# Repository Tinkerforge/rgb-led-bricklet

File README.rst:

RGB LED Bricklet
================

This repository contains the firmware source code and the hardware design
files. The documentation generator configs can be found at
https://github.com/Tinkerforge/generators

Repository Content
------------------

software/:
 * examples/: Examples for all supported languages
 * build/: Compiled files
 * src/: Source code of firmware
 * Makefile: Makefile to build project

hardware/:
 * Contains KiCad project files and additionally schematics as PDF

datasheets/:
 * Contains datasheets for sensors and complex ICs that are used

Hardware
--------

The hardware is designed with the open source EDA Suite KiCad
(http://www.kicad.org). Before you are able to open the files,
you have to install the Tinkerforge kicad-libraries
(https://github.com/Tinkerforge/kicad-libraries). You can either clone
them directly in hardware/ or clone them in a separate folder and
symlink them into hardware/
(ln -s kicad_path/kicad-libraries project_path/hardware). After that you
can open the .pro file in hardware/ with KiCad and from there view and
modify the schematics and the PCB layout.

Software
--------

If you want to do your own Brick/Bricklet firmware development we highly
recommend that you use our build environment setup script and read the
tutorial (https://www.tinkerforge.com/en/doc/Tutorials/Tutorial_Build_Environment/Tutorial.html).

To compile the C code we recommend you to install the newest GNU Arm Embedded
Toolchain (https://launchpad.net/gcc-arm-embedded/+download).
You also need to install bricklib (https://github.com/Tinkerforge/bricklib)
and brickletlib (https://github.com/Tinkerforge/brickletlib).

You can either clone it directly in software/src/ or clone it in a
separate folder and symlink it into software/src/
(ln -s bricklib_path/bricklib project_path/software/src/ and
ln -s brickletlib_path/brickletlib project_path/software/src/).
Finally make sure to have CMake installed
(http://www.cmake.org/cmake/resources/software.html).

After that you can build the firmware by invoking make in software/.
The firmware (.bin) can then be found in software/build/ and uploaded
with brickv (click button "Flashing" on start screen).

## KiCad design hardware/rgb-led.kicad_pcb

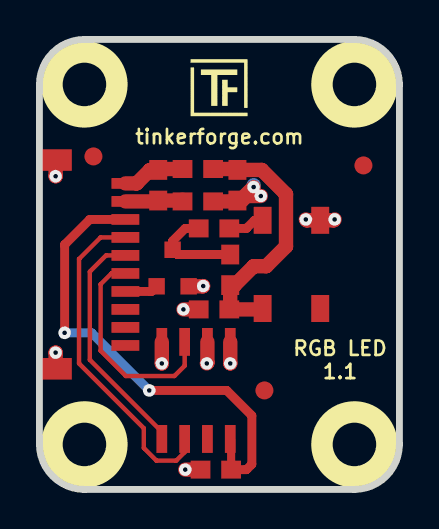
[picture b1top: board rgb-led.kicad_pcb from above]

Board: 2 copper layers, 20.0 x 25.0 mm, 20 parts (0 on the bottom side), 11 nets.

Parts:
C1, C2, C3, C4: 100nF; C0603E
FB1: FILTER; C0603E
Fiducial_Mark: VAL**; Fiducial_Mark
Fiducial_Mark#2, Fiducial_Mark#3: VAL**; Fiducial_Mark
LED1: WS2812B_LED
P1: CON-SENSOR
Q1: 2N7002P; SOT23GDS
R1: 1k; R0603E
R2: 0; R0603E
R3: 330; R0603E
U1: M24C64; SOIC8
U2, U3, U4, U5: DRILL; DRILL_NP
VAL: CE_5mm

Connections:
3V3: C4.1, P1.3, U1.8
GND: C2.1, C3.2, C4.2, LED1.3, P1.EP, Q1.S, R2.1, U1.1, U1.2, U1.4
unnamed: C1.1, P1.2, R2.2
unnamed: C1.2, FB1.1, P1.1
unnamed: LED1.4, R3.1
unnamed: P1.6, U1.3
unnamed: P1.7, Q1.G
unnamed: Q1.D, R1.1, R3.2
SCL: P1.4, U1.6
SDA: P1.5, U1.5
VCC: C2.2, C3.1, FB1.2, LED1.1, R1.2

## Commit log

2015-11-18 initial checkin of readme and license file
2015-11-18 prototype of rgb pixel bricklet
2015-11-23 fully routed, drc check
2016-02-09 Add WIP marker
2016-03-31 add fiducials
2016-06-10 Add RGB LED Bricklet plugin source
2016-06-10 Fix device identifier
2016-06-10 Add .gitignore
2016-06-17 add schematic
2016-06-27 Add examples
2016-07-01 Make the change UID comment more explicit
2016-07-13 Add changelog date and commit after the fact
2016-07-13 Add rainbow example
2016-07-13 Add WAS2812B datasheet
2016-07-14 Remove WIP marker
2016-08-04 fix rgb led bricklets dimensions
2016-08-04 increase version number to 1.1
2016-08-04 update schematic
2016-09-06 Fix green flash after reset
    MOSFET inverts logic, initial pin state needs to be high to ensure low
    output until first frame.
2016-09-06 Add changelog commit after the fact
2017-06-02 octave: Use javaObject instead of deprecated java_new
2017-08-01 Fix smybol
2017-08-01 Add 3d information (final)
2017-08-01 Add 3d model (*.step & *.FCStd)
2017-12-07 mathematica: Also generate .nb files
2018-02-19 javascript: Close div tag correctly
2018-02-20 Cleanup KiCad libraries config
    Ensure LibDir=kicad-libraries and LibName1=tinkerforge.
    Remove special library.
2018-05-24 perl: Use strict in examples
2018-07-11 Add Makefile with docker support
2018-07-11 Update directory structure and build instructions
2018-07-11 Remove obsolete generate_makefile scripts
2018-11-06 Add rust examples
2018-11-07 rust: Accept host names for ip connection, fix naming inconsistencies
2018-12-14 Add go examples.
2018-12-18 go: Change import path.
2018-12-18 go: Change import path again.
2018-12-20 rust: Reformat examples.
2019-01-24 mqtt: Add examples.
2019-01-24 mqtt: Fix example header.
2019-01-24 mqtt: Remove executable bit in example permissions.
2019-01-24 go: Minor example fixes.
2020-01-13 examples: Use python3 input instead of python2 raw_input.
2020-02-26 python: Update "Change UID" comment style
2020-03-16 Whitespace
2020-04-07 examples: rust: Always block when calling bindings functions.
2021-10-25 Update KiCad link
    https://www.kicad.org/blog/2021/10/Avoid-links-to-former-kicad-domain/
2022-07-06 Add license files.

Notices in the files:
hardware/rgb-led.kicad_pcb:
Licensed under CERN OHL v.1.1
Copyright (©) 2016, B.Nordmeyer
Copyright Tinkerforge GmbH 2016.
This documentation describes Open Hardware and is licensed under the
CERN OHL v. 1.1.
